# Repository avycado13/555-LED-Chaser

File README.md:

# 555-LED-Chaser
An led chaser using a 555 for Hack club's Stasis!

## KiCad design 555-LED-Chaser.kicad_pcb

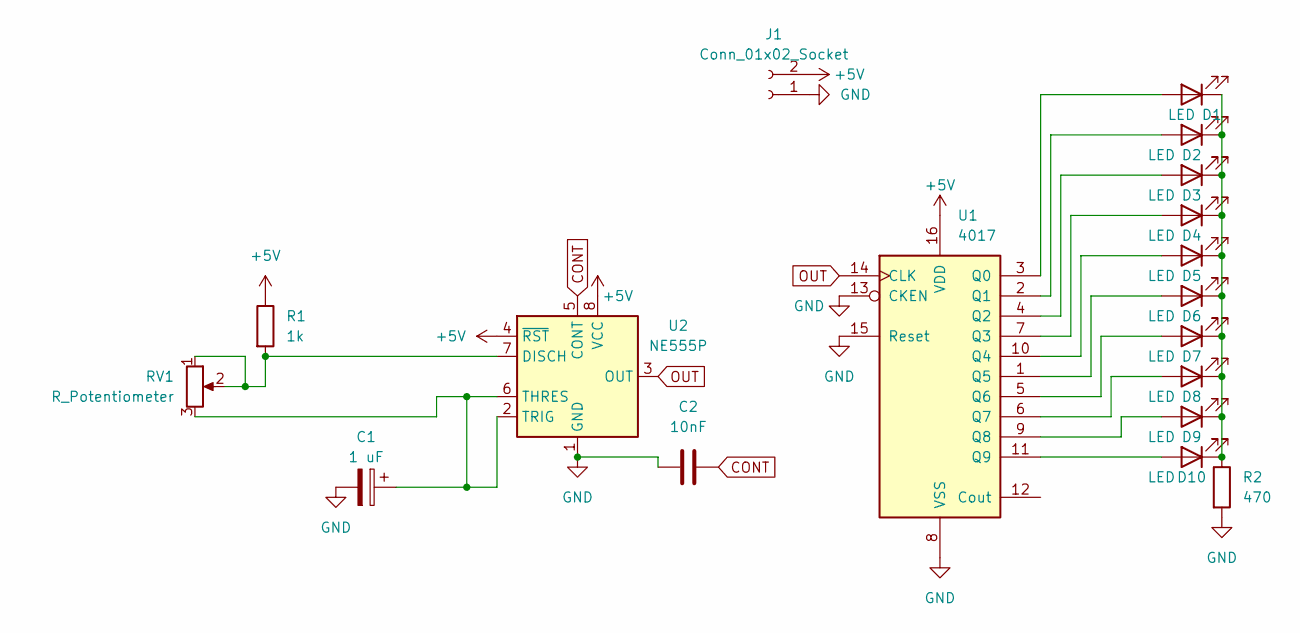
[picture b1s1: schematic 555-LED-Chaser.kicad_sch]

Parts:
C1: 1 uF; CP_Radial_D5.0mm_P2.50mm
C2: 10nF; C_Disc_D5.0mm_W2.5mm_P5.00mm
D1, D2, D3, D4, D5, D6, D7, D8, D9, D10: LED; LED_D5.0mm
J1: Conn_01x02_Socket; PinHeader_1x02_P2.54mm_Vertical
R1: 1k; R_Axial_DIN0207_L6.3mm_D2.5mm_P10.16mm_Horizontal
R2: 470; R_Axial_DIN0207_L6.3mm_D2.5mm_P10.16mm_Horizontal
RV1: R_Potentiometer; Potentiometer_Bourns_PTV09A-1_Single_Vertical
U1: 4017; DIP-16_W7.62mm
U2: NE555P; DIP-8_W7.62mm

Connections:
+5V: J1.2, R1.1, U1.16 (VDD), U2.4 (~RST), U2.8 (VCC)
CONT: C2.2, U2.5 (CONT)
GND: C1.2, C2.1, J1.1, R2.2, U1.8 (VSS), U1.13 (CKEN), U1.15 (Reset), U2.1 (GND)
unnamed: D1.2 (A), U1.3 (Q0)
unnamed: D1.1 (K), D2.1 (K), D3.1 (K), D4.1 (K), D5.1 (K), D6.1 (K), D7.1 (K), D8.1 (K), D9.1 (K), D10.1 (K), R2.1
unnamed: D2.2 (A), U1.2 (Q1)
unnamed: D3.2 (A), U1.4 (Q2)
unnamed: D4.2 (A), U1.7 (Q3)
unnamed: D5.2 (A), U1.10 (Q4)
unnamed: D6.2 (A), U1.1 (Q5)
unnamed: D7.2 (A), U1.5 (Q6)
unnamed: D8.2 (A), U1.6 (Q7)
unnamed: D9.2 (A), U1.9 (Q8)
unnamed: D10.2 (A), U1.11 (Q9)
unnamed: R1.2, RV1.1, RV1.2, U2.7 (DISCH)
unnamed: C1.1, RV1.3, U2.2 (TRIG), U2.6 (THRES)
OUT: U1.14 (CLK), U2.3 (OUT)

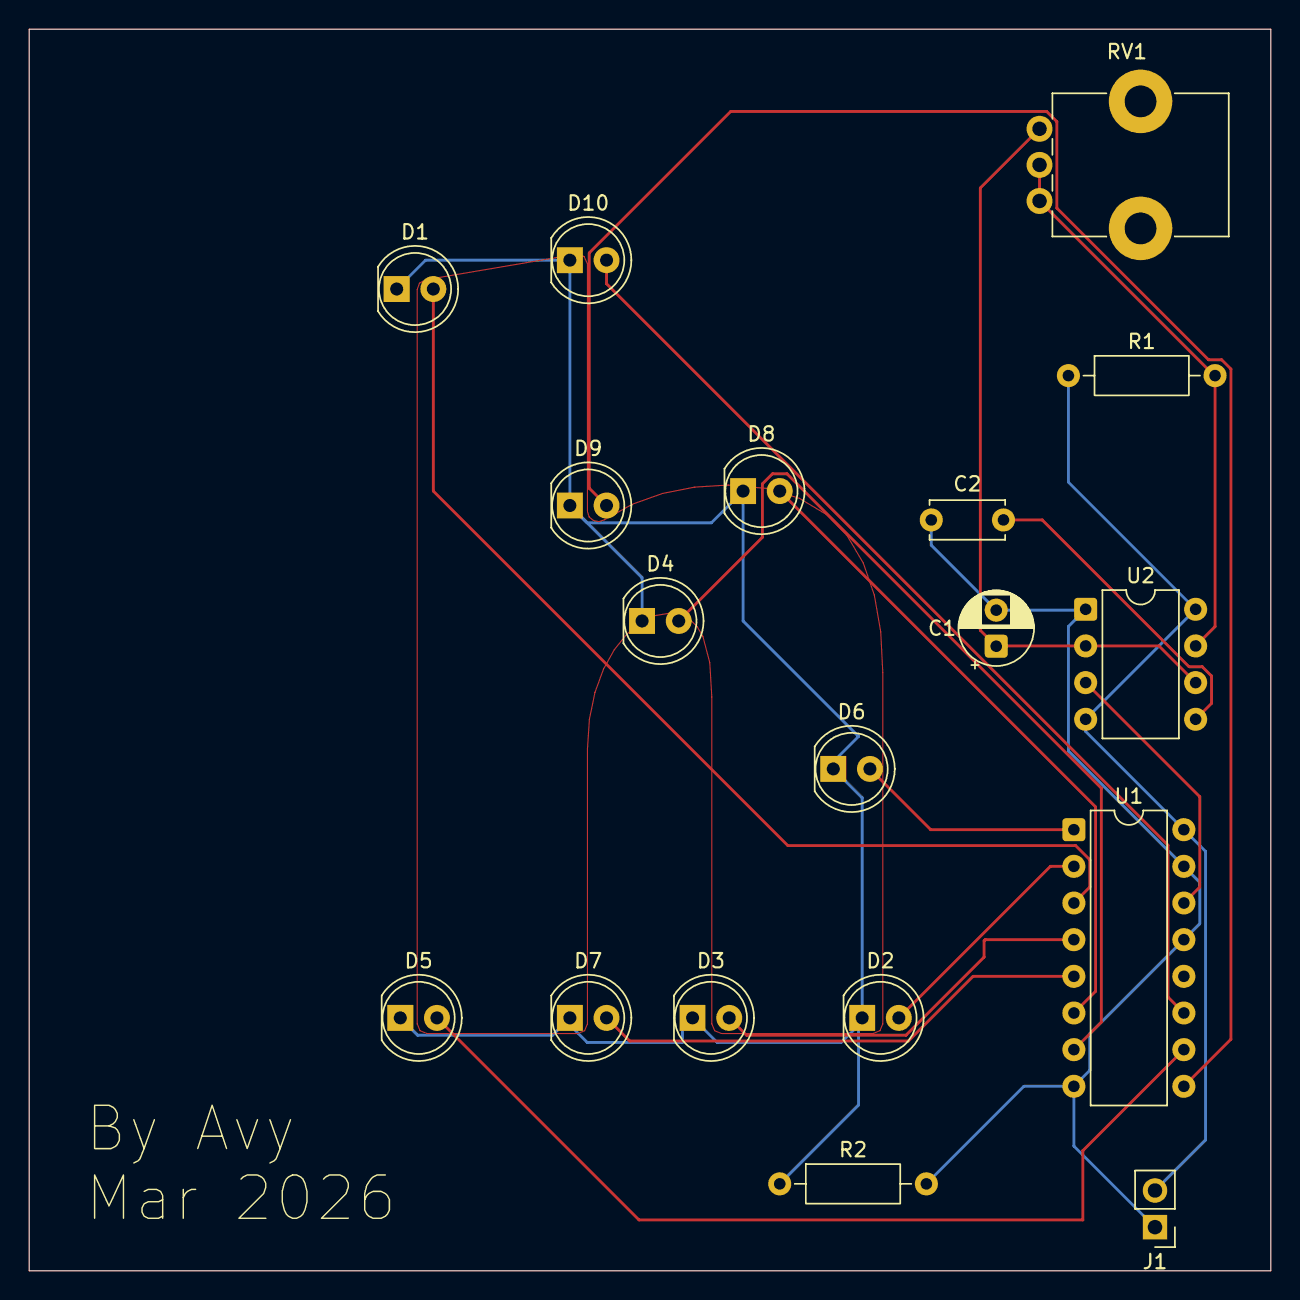
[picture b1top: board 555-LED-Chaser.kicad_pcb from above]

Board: 2 copper layers, 86.0 x 86.0 mm, 18 parts (0 on the bottom side), 17 nets.

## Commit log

2026-03-22 Finished PCB
